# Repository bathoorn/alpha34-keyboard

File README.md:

# alpha34-keyboard
kicad alpha34 keyboard project

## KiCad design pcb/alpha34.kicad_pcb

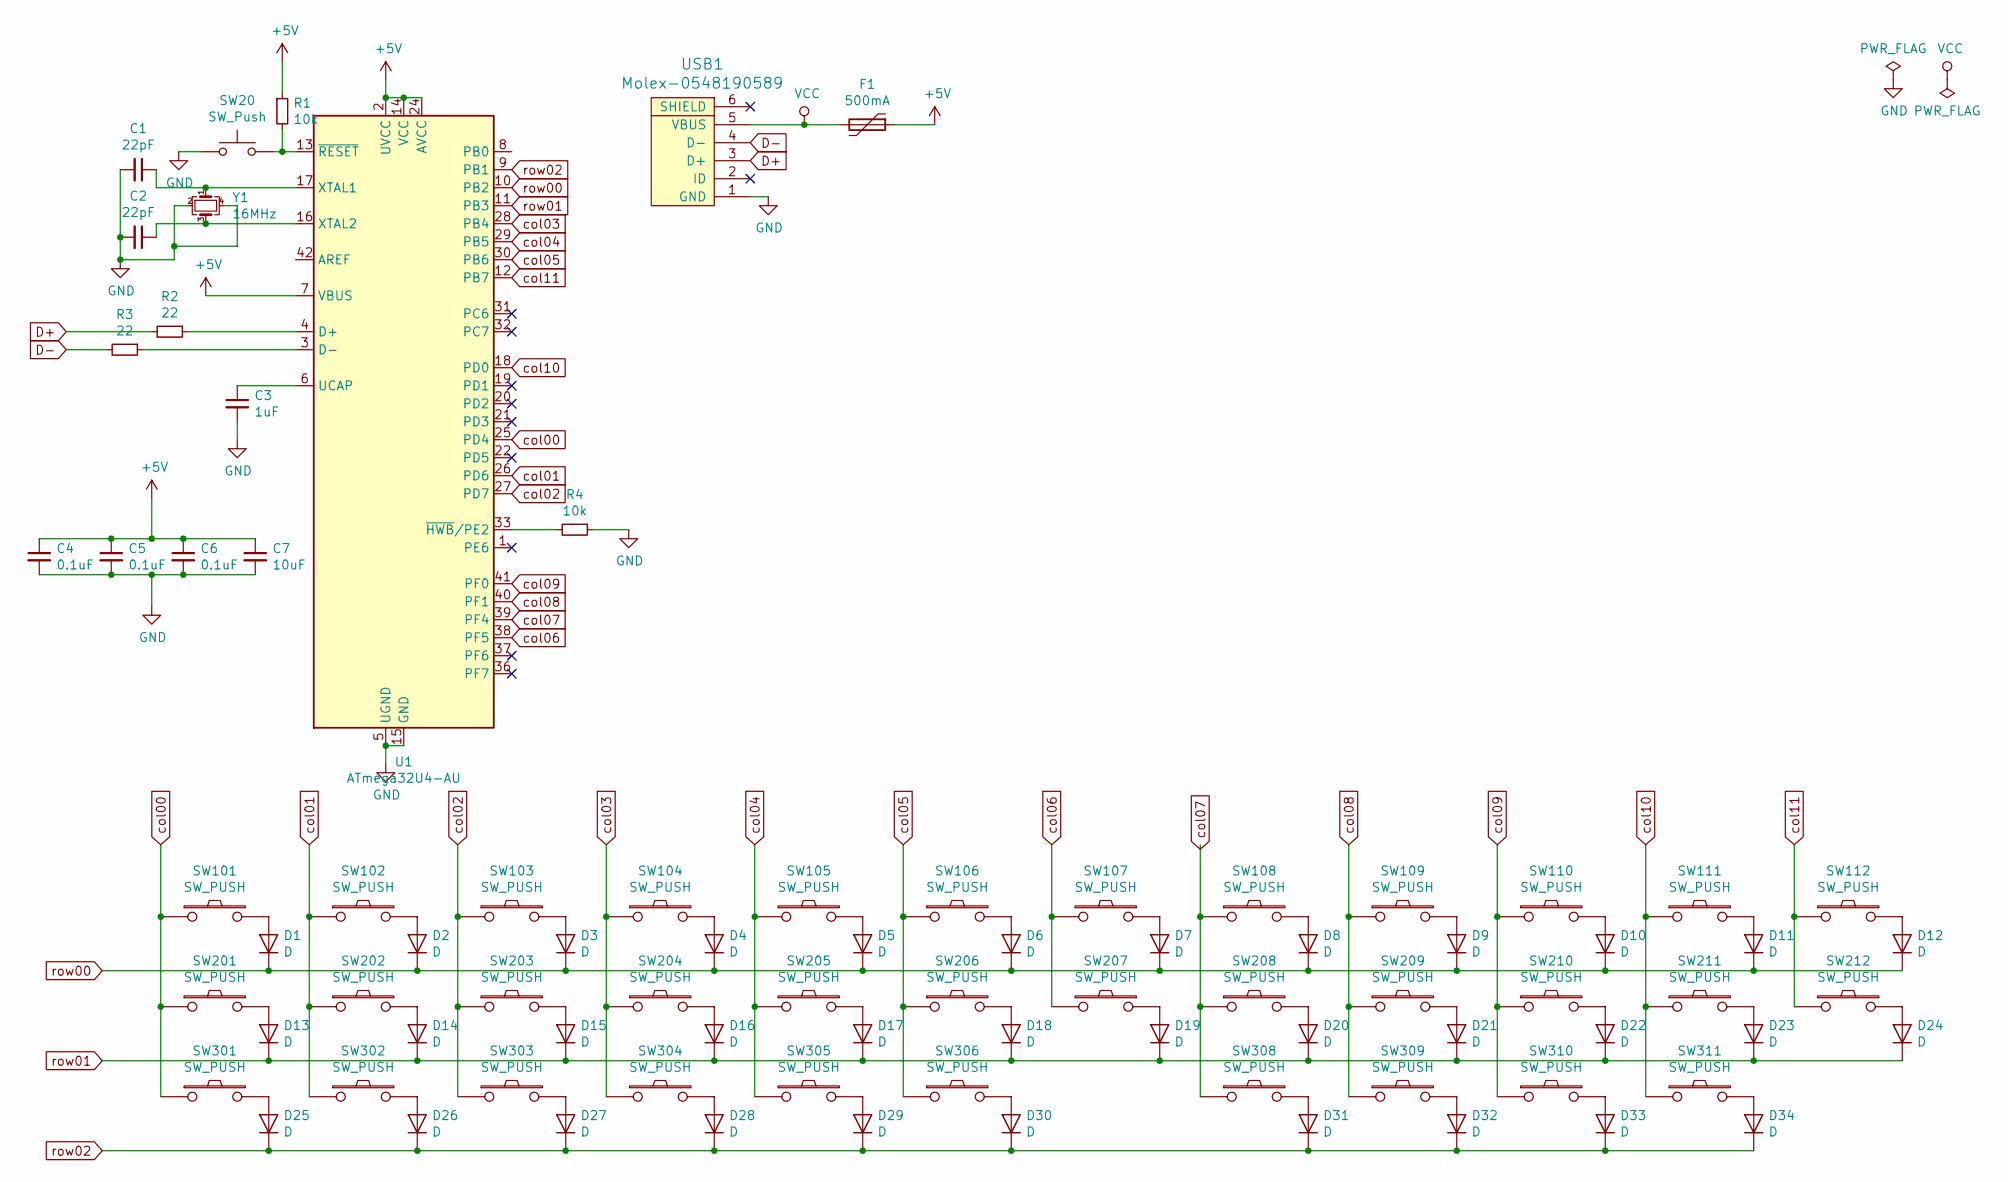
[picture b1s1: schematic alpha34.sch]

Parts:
C1, C2: 22pF; C_0805_2012Metric
C3: 1uF; C_0805_2012Metric
C4, C5, C6: 0.1uF; C_0805_2012Metric
C7: 10uF; C_0805_2012Metric
D1, D2, D3, D4, D5, D6, D7, D8, D9, D10, D11, D12, D13, D14, D15, D16, D17, D18, D19, D20, D21, D22, D23, D24, D25, D26, D27, D28, D29, D30, D31, D32, D33, D34: D; D3_SMD_Back
F1: 500mA; Fuse_1206_3216Metric
R1, R4: 10k; R_0805_2012Metric
R2, R3: 22; R_0805_2012Metric
SW20: SW_Push; SKQG-1155865
SW101, SW102, SW103, SW104, SW105, SW106, SW107, SW108, SW109, SW110, SW111, SW112, SW201, SW202, SW203, SW204, SW205, SW206, SW207, SW208, SW209, SW210, SW211, SW212, SW301, SW302, SW303, SW304, SW305, SW306, SW308, SW309, SW310, SW311: SW_PUSH; Kailh_socket_MX
U1: ATmega32U4-AU; TQFP-44_10x10mm_P0.8mm
USB1: Molex-0548190589; Molex-0548190589-fixed
Y1: 16MHz; Crystal_SMD_3225-4Pin_3.2x2.5mm

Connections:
+5V: C4.1, C5.1, C6.1, C7.1, F1.1, R1.1, U1.2 (UVCC), U1.7 (VBUS), U1.14 (VCC), U1.24 (AVCC), U1.34 (VCC), U1.44 (AVCC)
D+: R2.2, USB1.3 (D+)
D-: R3.2, USB1.4 (D-)
GND: C1.2, C2.2, C3.2, C4.2, C5.2, C6.2, C7.2, R4.1, SW20.1, U1.5 (UGND), U1.15 (GND), U1.23 (GND), U1.35 (GND), U1.43 (GND), USB1.1 (GND), Y1.2, Y1.4
unnamed: C1.1, U1.17 (XTAL1), Y1.1
unnamed: C2.1, U1.16 (XTAL2), Y1.3
unnamed: C3.1, U1.6 (UCAP)
unnamed: D1.2 (A), SW101.2
unnamed: D2.2 (A), SW102.2
unnamed: D3.2 (A), SW103.2
unnamed: D4.2 (A), SW104.2
unnamed: D5.2 (A), SW105.2
unnamed: D6.2 (A), SW106.2
unnamed: D7.2 (A), SW107.2
unnamed: D8.2 (A), SW108.2
unnamed: D9.2 (A), SW109.2
unnamed: D10.2 (A), SW110.2
unnamed: D11.2 (A), SW111.2
unnamed: D12.2 (A), SW112.2
unnamed: D13.2 (A), SW201.2
unnamed: D14.2 (A), SW202.2
unnamed: D15.2 (A), SW203.2
unnamed: D16.2 (A), SW204.2
unnamed: D17.2 (A), SW205.2
unnamed: D18.2 (A), SW206.2
unnamed: D19.2 (A), SW207.2
unnamed: D20.2 (A), SW208.2
unnamed: D21.2 (A), SW209.2
unnamed: D22.2 (A), SW210.2
unnamed: D23.2 (A), SW211.2
unnamed: D24.2 (A), SW212.2
unnamed: D25.2 (A), SW301.2
unnamed: D26.2 (A), SW302.2
unnamed: D27.2 (A), SW303.2
unnamed: D28.2 (A), SW304.2
unnamed: D29.2 (A), SW305.2
unnamed: D30.2 (A), SW306.2
unnamed: D31.2 (A), SW308.2
unnamed: D32.2 (A), SW309.2
unnamed: D33.2 (A), SW310.2
unnamed: D34.2 (A), SW311.2
unnamed: R1.2, SW20.2, U1.13 (~RESET)
unnamed: R2.1, U1.4 (D+)
unnamed: R3.1, U1.3 (D-)
unnamed: R4.2, U1.33 (~HWB~/PE2)
VCC: F1.2, USB1.5 (VBUS)
col00: SW101.1, SW201.1, SW301.1, U1.25 (PD4)
col01: SW102.1, SW202.1, SW302.1, U1.26 (PD6)
col02: SW103.1, SW203.1, SW303.1, U1.27 (PD7)
col03: SW104.1, SW204.1, SW304.1, U1.28 (PB4)
col04: SW105.1, SW205.1, SW305.1, U1.29 (PB5)
col05: SW106.1, SW206.1, SW306.1, U1.30 (PB6)
col06: SW107.1, SW207.1, U1.38 (PF5)
col07: SW108.1, SW208.1, SW308.1, U1.39 (PF4)
col08: SW109.1, SW209.1, SW309.1, U1.40 (PF1)
col09: SW110.1, SW210.1, SW310.1, U1.41 (PF0)
col10: SW111.1, SW211.1, SW311.1, U1.18 (PD0)
col11: SW112.1, SW212.1, U1.12 (PB7)
row00: D1.1 (K), D2.1 (K), D3.1 (K), D4.1 (K), D5.1 (K), D6.1 (K), D7.1 (K), D8.1 (K), D9.1 (K), D10.1 (K), D11.1 (K), D12.1 (K), U1.10 (PB2)
row01: D13.1 (K), D14.1 (K), D15.1 (K), D16.1 (K), D17.1 (K), D18.1 (K), D19.1 (K), D20.1 (K), D21.1 (K), D22.1 (K), D23.1 (K), D24.1 (K), U1.11 (PB3)
row02: D25.1 (K), D26.1 (K), D27.1 (K), D28.1 (K), D29.1 (K), D30.1 (K), D31.1 (K), D32.1 (K), D33.1 (K), D34.1 (K), U1.9 (PB1)

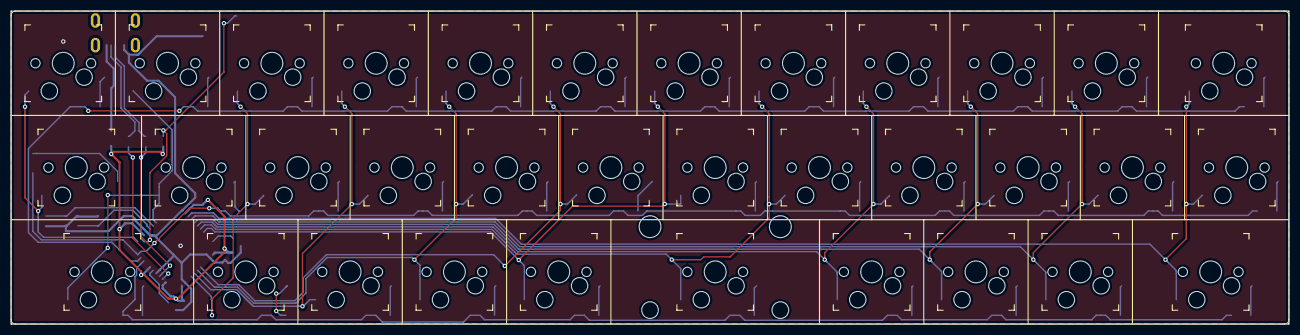
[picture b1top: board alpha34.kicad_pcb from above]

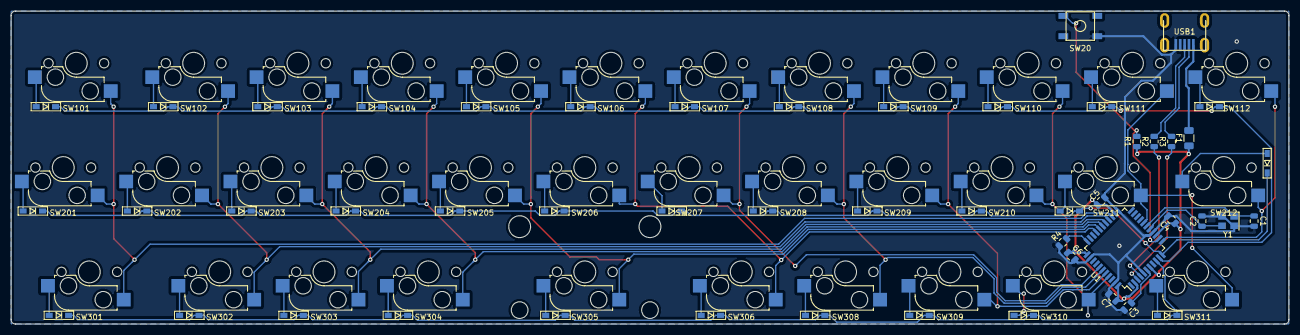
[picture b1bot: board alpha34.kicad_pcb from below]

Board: 2 copper layers, 233.4 x 57.2 mm, 84 parts (16 on the bottom side), 61 nets.

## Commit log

2020-04-01 add kicad files
2020-04-01 add parts
